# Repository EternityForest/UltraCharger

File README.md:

# UltraCharger
Highly experimental I2C solar battery charger frontend 

This little board is smaller than a buisiness card and basically acts as a frontend for ORing two inputs(2.1mm barrel),

putting the power through a buck-boost into a battery, measuring battery voltage and charge current, and providing 3.3v on the STEMMA
connector through a LDO regulator(Efficiency isn't an issue given the very low current needed to wake up one a second and do MPPT, and
occasionally report status).

There's no UI, it's meant for use with an ESP8266 breakout and UI via a remote machine.

This makes a ton of compromises to be smaller than a business card and on 2 layers. It's not tested and won't be till
I get the PCBs back. However it has been designed to be about as safe as any other consumer microcontroller-powered charger, when used
with the appropriate protection PCB for your battery.

The core is a 1A switching regulator set to 21V, for charging Ryobi One+ batteries. Even if the MCU fails it will not reach unsafe voltages.

That also should be witin the safe range of any decent 4S lithium protection PCB, unless they make thise crappier than I think,
so you should be able to charge 12V batteries and various LTO batteries.

You likely won't be getting more than 12-20 watts with this thing, and efficiency isn't fantastic, but it should be robust against all manner or transients and bad connections, aside from reverse battery which it handles with a clamp that trips the fuse or protection circuit you hopefully are using.

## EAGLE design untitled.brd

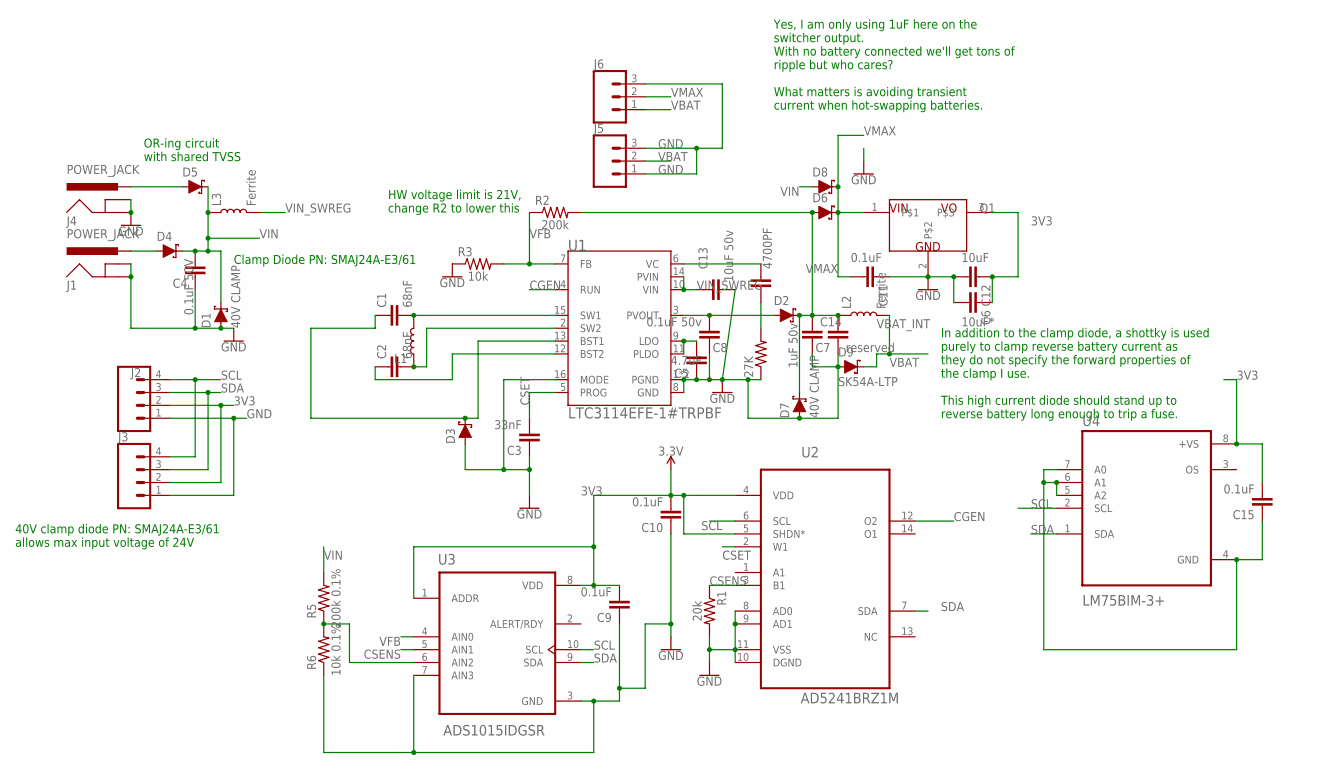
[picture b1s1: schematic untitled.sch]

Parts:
27K: 0805-EZ
4700PF: 1.0uF; 0805-EZ
C1, C2: 68nF; 0805-EZ
C3: 33nF; 0805-EZ
C4: 0.1uF 50V; 0805-EZ
C5: 4.7uF; 0805-EZ
C6: 10uF*; 0805-EZ
C7: reserved; 1206
C8: 0.1uF 50v; 0805-EZ
C9, C10, C11, C15: 0.1uF; 0805-EZ
C12: 10uF; 0805-EZ
C13: 10uF 50v; 1206
C14: 1uF 50v; 0805-EZ
D1, D7: 40V CLAMP; SMA-DIODE
D2, D3, D4, D5, D6, D8: 3A/40V/500mV; SMA-DIODE
D9: SK54A-LTP; SMA-DIODE
J1, J4: POWER_JACK; POWER_JACK_PTH
J2, J3: CONN_04JST-PTH-VERT; JST-4-PTH-VERT
J5, J6: CONN_03SCREW_LOCK; SCREWTERMINAL-3.5MM-3_LOCK.007S
L1: 27µH/±20%/3.3A; INDUCTOR_SDR1307
L2, L3: Ferrite; 0805
Q1: BD433M5FP-CE2TO252_STM; TO252_STM
R1: 20k; 0805-EZ
R2: 200k; 0805-EZ
R3: 10k; 0805-EZ
R5: 200k 0.1%; 0805-EZ
R6: 10k 0.1%; 0805-EZ
U1: LTC3114EFE-1#TRPBF; SOP65P640X110-17N
U2: AD5241BRZ1M; SOIC127P600X175-14N
U3: ADS1015IDGSR; SOP50P490X110-10N
U4: LM75BIM-3+; SOIC127P600X175-8N

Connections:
3V3: C6.1, C9.2, C10.2, C12.1, C15.2, J2.2, J3.2, Q1.3, U2.4 (VDD), U2.5 (SHDN*), U3.1 (ADDR), U3.8 (VDD), U4.8 (+VS)
CGEN: U1.4 (RUN), U2.12 (O2)
CSENS: R1.1, U2.3 (B1), U3.5 (AIN1)
CSET: C3.2, U1.5 (PROG), U2.2 (W1)
GND: 27K.1, C3.1, C4.1, C5.1, C6.2, C7.1, C8.1, C9.1, C10.1, C11.1, C12.2, C13.2, C14.2, D1.A, D3.A, D7.A, D9.A, J1.GND, J1.GNDBREAK, J2.1, J3.1, J4.GND, J4.GNDBREAK, J5.1, J5.3, J6.3, Q1.2, R1.2, R3.1, R6.1, U1.1 (PGND), U1.8 (GND), U1.16 (MODE), U1.17 (PGND), U2.8 (AD0), U2.9 (AD1), U2.10 (DGND), U2.11 (VSS), U3.3 (GND), U3.7 (AIN3)
unnamed: C1.2, L1.P$2 (2), U1.15 (SW1)
unnamed: C2.2, L1.P$1 (1), U1.2 (SW2)
unnamed: C1.1, D3.C, U1.13 (BST1)
unnamed: C2.1, U1.12 (BST2)
unnamed: D4.A, J1.PWR
unnamed: R5.1, R6.2, U3.6 (AIN2)
unnamed: C15.1, U4.4 (GND), U4.5 (A2), U4.6 (A1), U4.7 (A0)
unnamed: D5.A, J4.PWR
unnamed: C8.2, D2.A, U1.3 (PVOUT)
unnamed: C5.2, U1.9 (LDO), U1.11 (PLDO)
unnamed: 4700PF.2, U1.6 (VC)
unnamed: 27K.2, 4700PF.1
SCL: J2.4, J3.4, U2.6 (SCL), U3.10 (SCL), U4.2 (SCL)
SDA: J2.3, J3.3, U2.7 (SDA), U3.9 (SDA), U4.1 (SDA)
VBAT: D9.C, J5.2, J6.1, L2.2
VBAT_INT: C7.2, C14.1, D2.C, D6.A, D7.C, L2.1, R2.2
VFB: R2.1, R3.2, U1.7 (FB), U3.4 (AIN0)
VIN: C4.2, D1.C, D4.C, D5.C, D8.A, L3.1, R5.2
VIN_SWREG: C13.1, L3.2, U1.10 (VIN), U1.14 (PVIN)
VMAX: C11.2, D6.C, D8.C, J6.2, Q1.1

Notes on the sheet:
OR-ing circuit with shared TVSS
HW voltage limit is 21V, change R2 to lower this
40V clamp diode PN: SMAJ24A-E3/61 allows max input voltage of 24V
Yes, I am only using 1uF here on the switcher output. With no battery connected we'll get tons of ripple but who cares? What matters is avoiding transient current when hot-swapping batteries.
In addition to the clamp diode, a shottky is used purely to clamp reverse battery current as they do not specify the forward properties of the clamp I use. This high current diode should stand up to reverse battery long enough to trip a fuse.
Clamp Diode PN: SMAJ24A-E3/61

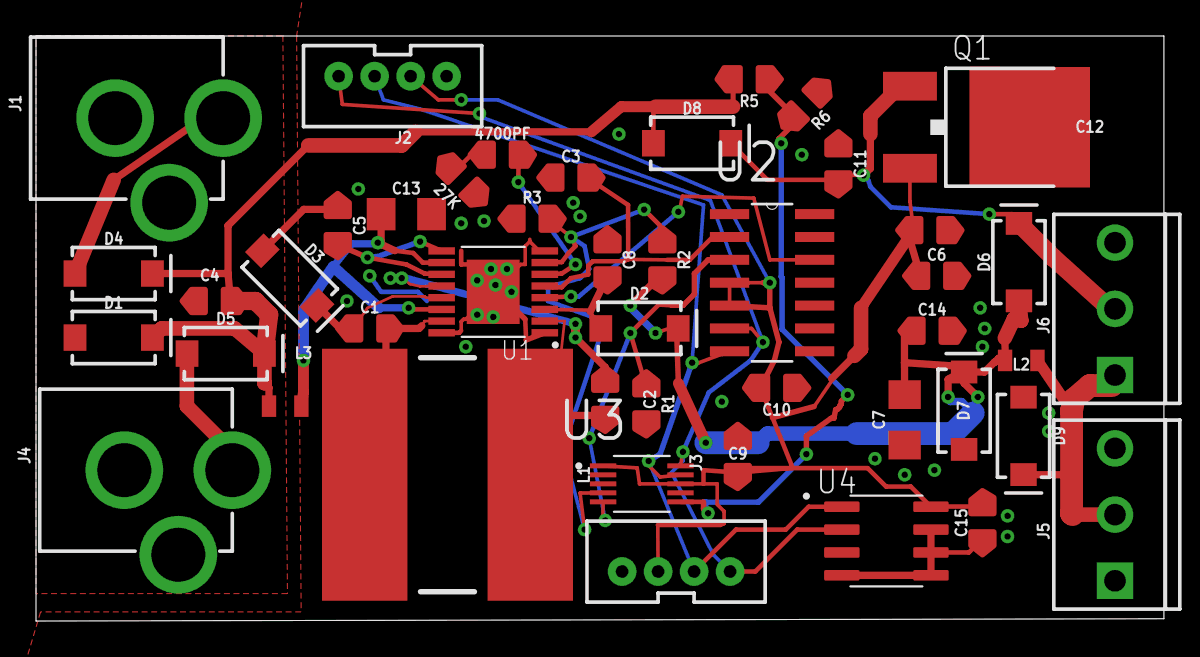
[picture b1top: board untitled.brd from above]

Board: 2 copper layers, 62.7 x 32.5 mm, 45 parts (0 on the bottom side), 25 nets.

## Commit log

2019-06-10 First Commit!

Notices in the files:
parts and their libraries:
SparkFun-Coils: Licensing: Creative Commons ShareAlike 4.0 International - https://creativecommons.org/licenses/by-sa/4.0
